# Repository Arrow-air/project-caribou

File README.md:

# Project Caribou 🦌

**An open-source heavy-lift hexacopter for cargo logistics and precision agriculture.**

Project Caribou is a ~200 kg MTOW hexacopter with ~100 kg payload capacity, 18–24S power architecture, and ArduPilot firmware. Designed for ruggedness, field repairability, and cost-effective manufacturing. Built on lessons from Project Feather and Project Quiver.

Developed by [Arrow Air](https://arrowair.com) and released under the CERN Open Hardware Licence.

## Key Features

- **Heavy lift** — ~100 kg payload for cargo delivery or 80L liquid spraying
- **Hybrid material airframe** — welded steel/aluminum core with detachable CF or aluminum motor arms
- **High-voltage architecture** — 18–24S (60–100V) with external HV kill switch and redundant power supply
- **Redundant avionics** — triple-redundant IMU, GPS, and compass
- **ArduPilot firmware** — standard QGroundControl/Mission Planner compatibility
- **Field serviceability** — modular arms for transport, replaceable components

## Repository Structure

```
project-caribou/
├── engineering/            # Active design work
│   ├── cad/                # build123d CAD, reference geometry, exports
│   └── electronics/        # Self-contained KiCad PCB projects
│       └── pcbs/
│           ├── CBC_PCB/    # Caribou battery connector PCB, issue #6
│           │   └── kicad/libs/
│           └── CMAIN_PCB/  # Caribou main PCB, issue #8
│               └── kicad/libs/
├── docs/
│   ├── ADRs/               # Architecture Decision Records
│   └── meetings/           # Meeting notes and summaries
├── src/                    # Legacy/general source area
└── CONTRIBUTING.md
```

## Community

- **Discord** — [discord.gg/arrow](https://discord.gg/arrow) — `#project-caribou-general`
- **DAO Forum** — [dao.arrowair.com](https://dao.arrowair.com)

## License

Everything in this repository is licensed under the **[CERN Open Hardware Licence Version 2 - Strongly Reciprocal (CERN-OHL-S v2)](LICENSE)**: the hardware design (CAD files, schematics, PCB layouts, manufacturing files and documentation) and the CBC firmware under `engineering/electronics/pcbs/CBC_PCB/firmware/`. The licence requires that derivative works remain open source under the same terms.

Source location: <https://github.com/Arrow-air/project-caribou>

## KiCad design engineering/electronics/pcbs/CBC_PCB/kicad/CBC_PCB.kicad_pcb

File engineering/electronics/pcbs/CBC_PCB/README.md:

# CBC_PCB — Caribou Battery Connector PCB

The Caribou Battery Connector PCB (CBC) interfaces 18S smart battery packs with the Caribou hexacopter electrical system. Each motor arm carries one CBC board connected to one battery, providing power switching, protection, voltage regulation, and dual CAN bus communication.

- **GitHub issue:** [#6 — Design BC-PCB for Caribou: 18S, 100A nominal, 200A spike](https://github.com/Arrow-air/project-caribou/issues/6)
- **Starting point:** Project Quiver BC-PCB KiCad design.
- **EDA Tool:** KiCad 10
- **Initial layout import:** KiCad source is in [`kicad/`](kicad/); import notes are in [`docs/import-2026-05-19-cbc-layout.md`](docs/import-2026-05-19-cbc-layout.md).

## Context within Project Caribou

Project Caribou is a ~200 kg MTOW heavy-lift hexacopter with ~100 kg payload capacity, 18–24S power architecture, and ArduPilot firmware. The aircraft uses 6× Hobbywing XRotor X15 propulsion units, each fed by a dedicated 18S Tattu 4.0 smart battery.

Each of the 6 motor arms has:
- 1× Tattu 4.0 18S battery pack
- **1× CBC_PCB** (this board) — battery interface, protection, regulation
- 1× Hobbywing XRotor X15 motor + ESC

The CBC board sits between the battery and the propulsion unit. It provides:
1. **Battery interface** — receives battery power and battery CAN via the [C90D adapter PCB](../C90D_PCB/), which mates the Tattu 4.0 battery connector
2. **Short-circuit protection** — 250A ceramic fuse
3. **Active power switching** — precharge, kill switch, power enable via MOSFETs
4. **Voltage regulation** — galvanically isolated 12V (GNDE) for the aircraft power distribution, plus non-isolated 5V/3.3V (GNDI) for onboard logic
5. **Dual CAN bus** — battery protocol (CAN 1) and DroneCAN (CAN 2) as bridge
6. **Wireless diagnostics** — WiFi/BLE via ESP32-S3 for configuration and monitoring

The regulated 12V output (GNDE) feeds into the Caribou Main PCB ([CMAIN_PCB](../CMAIN_PCB/)) via the JST JWPF signal connector (J501) harness.

## Concept Renderings

These early renderings show the intended CBC_PCB packaging concept and approximate component placement. They are illustrative only and may change during schematic/layout development.

## Board Overview

```
Battery (18S Tattu 4.0)
        |
        v
+---------------------+
|  C90D Adapter PCB    |  ← Separate board: mates the battery connector,
|  (../C90D_PCB/)      |     bridges present-detect pins
+---------------------+
        |
        v
+---------------------+
|  Power Entry Pads    |  ← Power (+ / −) via HC201/HC202 pads,
|  + Battery CAN       |     CAN L/H from battery via CN201
+---------------------+
|  AMXL-250 Fuse       |  ← 250A short-circuit protection
+---------------------+
|  MOSFETs             |  ← Precharge / Kill switch / Power enable
+---------------------+
|  Screw Terminals     |  ← Red (+) and Black (−) cables
|  (AMT0650009DB0000G) |     to Hobbywing X15 propulsion
+---------------------+
|                       |
|  HV Bus (54–75.6V)   |
|    |            |     |
|    v            v     |
|  [Buck]    [Push-Pull]|
|  5V/1A     12V/10A   |
|  (GNDI)    (isolated) |
|    |        (GNDE)    |
|    v            |     |
|  [LDO]         |     |
|  3.3V          |     |
|  (GNDI)        |     |
+---------------------+
|  JST JWPF Connector  |  ← 12V (GNDE), DroneCAN, signals
|  (J501, 8-pos)       |     to aircraft harness → CMAIN_PCB
+---------------------+
```

## Specifications

| Parameter | Value |
|---|---|
| Configuration | 18S (18 series cell groups) |
| Max Voltage | 75.6V (4.2V × 18) |
| Nominal Voltage | 64.8V (3.6V × 18) |
| Continuous Current | 150A (in line with the C90D power path) |
| Spike Current | 200A (short duration) |
| Board Shape | Rectangular |
| EDA Tool | KiCad 10 |
| Board Layers | TBD |

### Current Rating Justification

Based on the Hobbywing XRotor X15 motor data:

| Throttle | Thrust | Current per Motor |
|---|---|---|
| 51% | 27,257 g | 44.7 A |
| 72% | 47,933 g | 101.6 A |
| 100% | 72,647 g | 197.1 A |

Hover throttle is ~50%. The 150A continuous rating covers normal operations with margin; the 200A spike rating handles full-throttle bursts.

## Connectors and Fuse

### Battery Interface (via C90D Adapter)

The CBC does not mate the battery directly. The Tattu 4.0 pack connector mates with the [C90D adapter PCB](../C90D_PCB/), which carries the battery connector (ACES 59626), bridges the battery-present detection pins, and adapts the connector orientation into the CBC assembly.

From the C90D, the battery reaches the CBC through:

| Interface | Reference | Function |
|---|---|---|
| Power entry pads | HC201 (`H_PWR-IN`), HC202 (`H_PWR-IN--PREFUSE`) | High-current + / − power path from the C90D |
| Battery CAN connector | CN201 (A1257WV-S-2P, 2-pin GH-compatible) | `CANH_BAT` / `CANL_BAT` to the isolated battery CAN interface |

> **Note:** the battery-present detection bridge (required for the Tattu pack to power on) lives on the C90D side — see the C90D documentation for connector and mating details.

### Propulsion Screw Terminals

**Selected: Amphenol Anytek AMT0650009DB0000G**

These are the high-current screw terminals where cables to the Hobbywing X15 propulsion system are connected (+ and −).

| Parameter | Value |
|---|---|
| Type | Screw Terminal, Power Tap |
| Screw Size | M5 |
| Pins | 6 |
| Current Rating | 180A |
| Mounting | Through-Hole DIP |
| Contact Material | Brass + Steel Nut (matte tin plated) |
| Torque | 18 lbf·in |

Two sets of AMT0650009DB0000G screw terminals are used on the board: one pair for the propulsion output (+ / −), and another pair for mounting the main fuse.

### Signal Connector (Drone Interface)

**Selected: JST B08B-JWPF-SK-R (J501)**

This connector interfaces the CBC with the rest of the Caribou electrical system via a wiring harness to the [CMAIN_PCB](../CMAIN_PCB/). The JWPF series is a waterproof wire-to-board connector family; an earlier Amphenol AT13 concept was dropped in favor of JST.

| Pin | Signal | Function |
|---|---|---|
| 1 | GNDE | Isolated ground |
| 2 | GNDE | Isolated ground |
| 3 | 12V_ISOLATED | Isolated 12V output to aircraft LV system |
| 4 | 12V_ISOLATED | Isolated 12V output to aircraft LV system |
| 5 | CANL_DRONE | DroneCAN low |
| 6 | CANH_DRONE | DroneCAN high |
| 7 | 12V_TRIGGER_SIG | Kill switch trigger signal |
| 8 | 12V_SUPPLY | 12V supply input |

The 8 positions carry the isolated 12V output (GNDE), the DroneCAN bus pair, and the kill/control signals to/from the Caribou avionics.

### Main Fuse (Short-Circuit Protection)

**Selected: Eaton AMXL-250**

The main fuse sits between the battery connector and the power output stage, protecting against short circuits. It is mounted on two AMT0650009DB0000G screw terminals (bolt-in design).

| Parameter | Value |
|---|---|
| Type | Automotive bolt-in fuse |
| Current Rating | 250A |
| Voltage Rating | 125 Vdc |
| Body | Ceramic |
| Mounting | Bolt-in (M5 terminals) on 2× AMT0650009DB0000G |

The 250A fuse rating provides short-circuit protection while allowing the full 200A spike current without nuisance blowing. The ceramic body handles the thermal demands of high-current interruption.

## MCU and Communication

### MCU: ESP32-S3-WROOM-1 (U301)

The ESP32-S3-WROOM-1 module (N16R8 variant) is a dual-core microcontroller with integrated wireless connectivity. It includes a PCB antenna — no external antenna components are required. A keepout zone must be maintained around the antenna area on the PCB layout (no copper / ground plane underneath).

| Parameter | Value |
|---|---|
| Core | 2× 32-bit Xtensa LX7, up to 240 MHz |
| Flash | 16 MB (N16R8) |
| PSRAM | 8 MB (N16R8) |
| WiFi | 802.11 b/g/n (2.4 GHz) |
| Bluetooth | BLE 5.0 |
| Operating Voltage | 3.0–3.6V |
| Antenna | Integrated PCB antenna |

### Dual CAN Bus (2× MCP2515 + Transceiver)

Two independent CAN networks using external MCP2515 controllers on a shared SPI bus. This provides identical timing behavior on both buses and clean separation of the battery-side and drone-side CAN domains.

| CAN Bus | Purpose | Controller | Transceiver |
|---|---|---|---|
| CAN 1 — Battery | Battery protocol (smart battery communication) | MCP2515 (U402, SPI, CS1) | ADM3053BRWZ (U404, galvanically isolated) |
| CAN 2 — Drone | DroneCAN (UAVCAN v0) interface to Caribou avionics | MCP2515 (U401, SPI, CS2) | TJA1049T/3J (U403) |

The battery CAN transceiver (ADM3053) has an integrated isolated DC-DC converter, so the battery-side CAN domain is galvanically isolated from the board logic. Each MCP2515 is clocked by a 16 MHz crystal (X401/X402). 120 Ω termination resistors are jumper-selectable and open by default.

The board converts between the battery protocol (CAN 1) and DroneCAN (CAN 2). The DroneCAN bus connects via the J501 signal connector through the wiring harness to the [CMAIN_PCB](../CMAIN_PCB/), which serves as the central avionics hub for all 6 motor arms.

### Schematic Sheet Interfaces

| Signal / rail | Source sheet | Destination sheet(s) | Direction / notes |
|---|---|---|---|
| `H_PWR-IN`, `H_PWR-IN-`, `H_PWR-IN--PREFUSE` | POWER SECTION | POWER SECTION / board power path | 18S battery high-current domain; main fuse is mounted on two of the AMT screw terminals (J201–J204). |
| `+5V` | POWER REGULATOR | ESP32 SECTION, CAN SECTION, PERIPHERALS | Internal non-isolated logic rail. |
| `+3V3` | POWER REGULATOR | ESP32 SECTION, CAN SECTION, PERIPHERALS | ESP32, MCP2515, CAN transceivers, sensors. |
| `12V_ISOLATED` | POWER REGULATOR | PERIPHERALS / J501 connector | Isolated output to aircraft harness; add an output fuse before harness output. |
| `ESP_ENABLE_SIGNAL` | ESP32 SECTION | POWER SECTION | ESP-controlled main MOSFET latch enable (latch: `U201` 74LVC2G02); latch output default-low via `R207` pulldown. |
| `PRECHARGE_ESP_SIGNAL` | ESP32 SECTION | POWER SECTION | ESP-controlled precharge command. |
| `SCHMITT_OUT` | POWER SECTION | ESP32 SECTION | Hardware kill/trigger state feedback to ESP32. |
| `SCK`, `MOSI`, `MISO` | ESP32 SECTION / CAN SECTION | ESP32 ↔ dual MCP2515 | Shared SPI bus; `SCK`/`MOSI` from ESP32, `MISO` from MCP2515s. |
| `CS#1`, `CS#2` | ESP32 SECTION | CAN SECTION | MCP2515 chip-selects; add pull-ups so controllers remain deselected during ESP32 reset/boot. |
| `INT#1`, `INT#2` | CAN SECTION | ESP32 SECTION | MCP2515 interrupt outputs; ESP32 pull-up usage is documented in firmware/hardware notes. |
| `RESET1`, `RESET2` | ESP32 SECTION | CAN SECTION | MCP2515 resets from ESP32. |
| `TEMP1_DQ`, `TEMP2_DQ` | ESP32 SECTION / PERIPHERALS | ESP32 ↔ temperature sensors | 1-Wire data nets; formerly `DATA1` / `DATA2`. |
| `CANH_BAT`, `CANL_BAT` | CAN SECTION / POWER SECTION | Battery connector ↔ CAN 1 | Battery CAN pair only; no battery CAN ground is normally carried. |
| `CANH_DRONE`, `CANL_DRONE` | CAN SECTION / PERIPHERALS | CAN 2 ↔ J501 harness | DroneCAN pair to CMAIN_PCB; termination is jumper-selectable and normally open. |
| `GND_CA`, `GND_CB`, `GNDI`, `GNDE` | Multiple | Domain-specific returns | `GND_CA` is effectively unused unless battery CAN reference is later required. `GND_CB` may be tied with other CBC `GND_CB` references on CMAIN_PCB. |

### GPIO Allocation

As routed on the ordered board (from the production netlist):

| Function | Signal | ESP32-S3 GPIO |
|---|---|---|
| Precharge command | `PRECHARGE_ESP_SIGNAL` | IO4 |
| Kill/trigger state feedback | `SCHMITT_OUT` | IO5 |
| Main MOSFET latch enable | `ESP_ENABLE_SIGNAL` | IO6 |
| Temperature sensors (1-Wire, DS18B20) | `TEMP2_DQ` / `TEMP1_DQ` | IO7 / IO15 |
| Shared SPI — MOSI, SCK, MISO | `MOSI` / `SCK` / `MISO` | IO11 / IO12 / IO13 |
| MCP2515 #1 (Battery CAN) — CS, INT, RESET | `CS#1` / `INT#1` / `RESET1` | IO10 / IO21 / IO48 |
| MCP2515 #2 (Drone CAN) — CS, INT, RESET | `CS#2` / `INT#2` / `RESET2` | IO14 / IO47 / IO9 |

## Functional Requirements

### Power Path

- **High-side MOSFET switching** — N-channel MOSFETs with charge pump gate drive
- **Precharge circuit** — soft-start via resistor + relay/MOSFET to limit inrush current
- **Emergency kill switch** — hardware-level kill input, independent of MCU. Connects to the Caribou external HV kill switch via the AT signal connector.
- **Main fuse** — Eaton AMXL-250 (250A) bolt-in fuse for short-circuit protection

### Voltage Regulation

The power supply architecture uses two independent stages with full galvanic isolation between internal onboard logic (GNDI) and external drone systems (GNDE).

#### Internal Supply (GNDI — non-isolated)

Provides power for onboard logic (ESP32, MCP2515, CAN transceivers, gate drivers, sensors).

| Stage | Topology | IC | Input | Output | Notes |
|---|---|---|---|---|---|
| 5V Rail | Sync Buck | e.g. MP9487 or similar (100V+, integrated FETs, ≥1A) | 54–75.6V (HV Bus) | 5V / 1A | Main internal rail |
| 3.3V Rail | LDO | e.g. AMS1117-3.3 or similar | 5V | 3.3V | ESP32, MCP2515, CAN transceivers |

#### External Supply (GNDE — galvanically isolated)

Provides isolated 12V output for the Caribou aircraft power distribution via the [CMAIN_PCB](../CMAIN_PCB/).

| Stage | Topology | IC | Input | Output | Notes |
|---|---|---|---|---|---|
| 12V Rail | Isolated Push-Pull | TBD | 54–75.6V (HV Bus) | 12V / 10A (isolated, GNDE) | Powers aircraft avionics, sensors, servos via CMAIN_PCB |

The isolation barrier between GNDI and GNDE ensures that a fault on the aircraft power bus does not back-feed into the battery management logic.

## Folder Layout

```
CBC_PCB/
├── README.md               ← this file
├── docs/                   ← board-specific notes, requirements, design docs
│   ├── connector-pinout.md ← connector/harness pinout and wiring notes
│   ├── power-architecture.md ← power tree and protection notes
│   ├── pt1.5-changes.md    ← PT1.5 changes: precharge ground fix, sensing, buzzer, aux inrush
│   └── schematic-review-followup.md ← schematic review action register
├── firmware/               ← board-specific firmware (ESP32-S3)
├── images/                 ← board renders, screenshots, diagrams, photos
├── kicad/                  ← KiCad 10 project files
│   ├── libs/               ← project-local KiCad libraries
│   │   ├── 3dmodels/       ← project-local 3D models
│   │   ├── CBC_PCB.pretty/ ← project-local footprint library
│   │   └── CBC_PCB.kicad_sym ← project-local symbol library
│   └── production/         ← JLC fab outputs: Gerber zip, BOM, positions, netlist
└── manufacturing/          ← board STEP (zipped, CBC_PCB.step.zip) and fab toolkit options
```

## Related

- [CMAIN_PCB](../CMAIN_PCB/) — Caribou Main PCB (central avionics hub)
- [Project Caribou](https://github.com/Arrow-air/project-caribou) — parent project
- [Issue #6](https://github.com/Arrow-air/project-caribou/issues/6) — tracking issue for this board
- [Issue #8](https://github.com/Arrow-air/project-caribou/issues/8) — CMAIN_PCB tracking issue

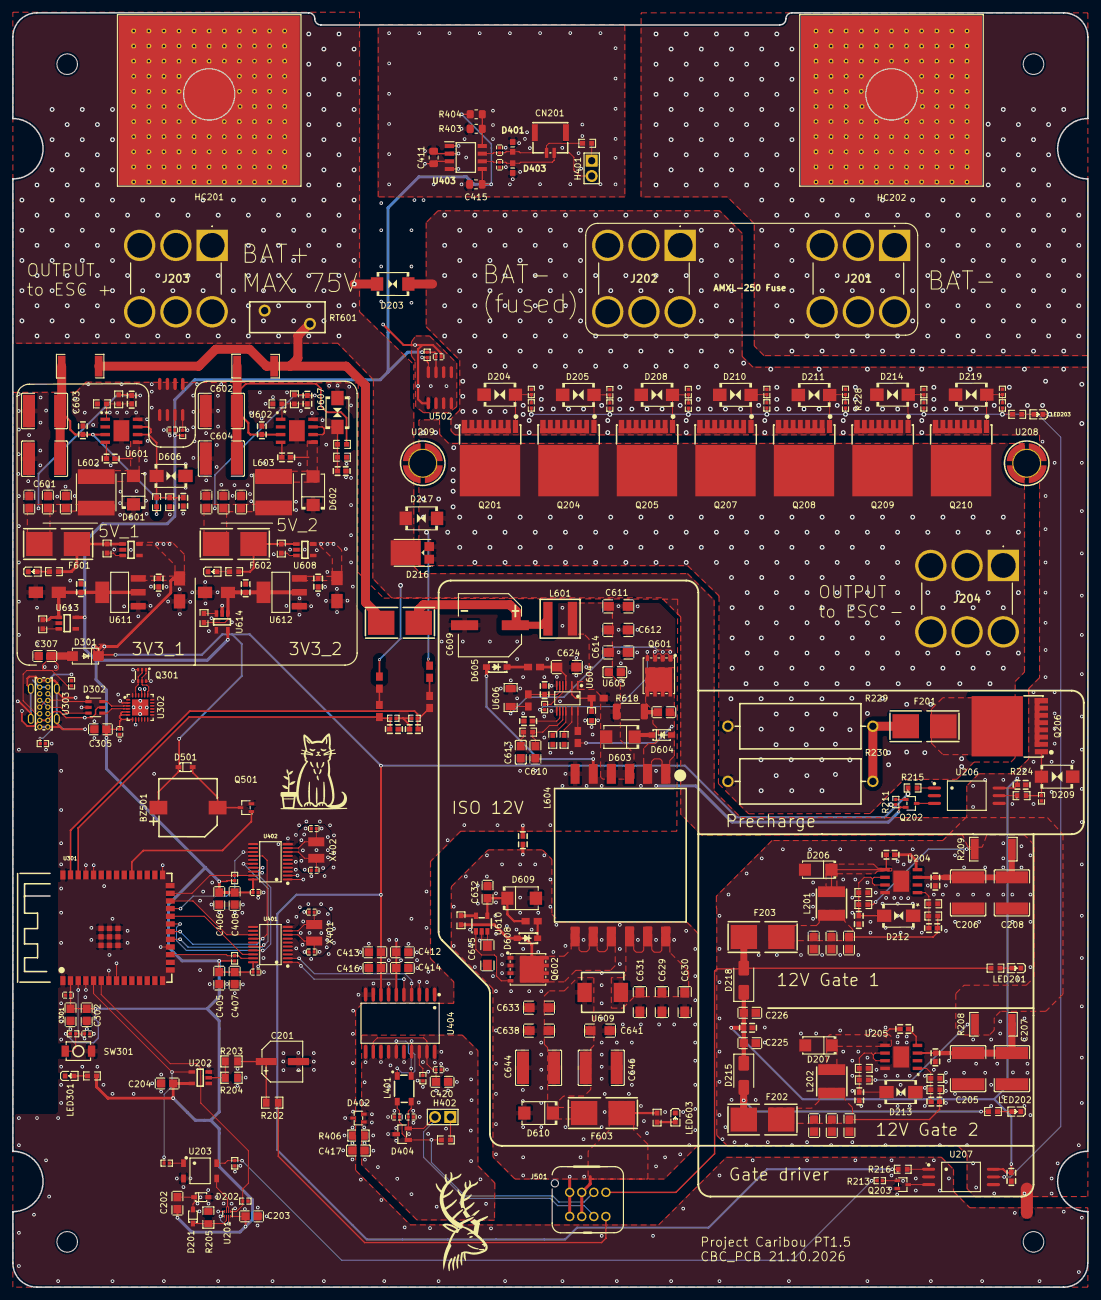
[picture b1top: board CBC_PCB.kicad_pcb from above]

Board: 6 copper layers, 178.0 x 211.0 mm, 317 parts (0 on the bottom side), 159 nets.

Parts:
BZ501: GSD9605YB-5V2800; BUZ-SMD_GSD9605YB-5V2800
C201: 100uF; CAP-SMD_BD6.3-L6.6-W6.6-LS7.4-FD
C202, C632: 1uF; C0805
C203, C204, C302, C305, C307, C407, C408, C414, C416, C420: 10uF; C0805
C205, C206, C207, C208, C601, C602, C603, C604, C644, C646: 2.2uF; C2220
C209, C210, C211, C212, C213, C214, C215, C216, C223, C224, C227, C228, C229, C605, C606, C607, C608, C616, C617, C626, C627, C634, C635, C639, C640: 100nF; C0603
C217, C218, C219, C220, C221, C222, C225, C226, C301, C405, C406, C412, C413, C618, C619, C620, C621, C622, C623: 4.7uF; C0805
C303: 1uF; C0402
C304, C306, C409, C410, C421, C501, C502: 100nF; C0402
C401, C402, C403, C404: 22pF; C0402
C411, C415: 100nF; C_0805_2012Metric_Pad1.18x1.45mm_HandSolder
C417: 100pF; C0805
C418, C419, C422, C423: 220pF; C0402
C609: 47uF; CAP-SMD_BD10.0-L10.3-W10.3-FD-LS11.0
C610: 470pF; C0805
C611, C612, C614, C624, C645: 4.7uF; C1206
C613: 33nF; C0805
C615: 220nF; C0603
C625: 47pF; C0603
C628: 4.7nF; C0603
C629, C630, C631, C633, C638, C641: 47uF; C1206
C636, C637, C642, C643: 10uF; CAP-SMD_L3.5-W2.8-R-RD
CN201: CONN-SMD_A1257WV-S-2P
D201, D202: SOD-323_L1.8-W1.3-LS2.5-RD
D203, D217: SMBJ78CA; SMB_L4.3-W3.6-LS5.4-BI
D204, D205, D208, D209, D210, D211, D214, D219: SMB_L4.6-W3.6-LS5.4-BI
D206, D207: SMA_L4.3-W2.6-LS5.2-RD
D212, D213, D606, D607: SMB_L4.6-W3.6-LS5.3-BI
D215, D218: SS34; D_SMA
D216: FSV10150V; C719814_TO-277A_L5_9-W4_4-LS6_5-TR
D301: SMA_L4.3-W2.6-LS5.0-FD
D302: SOT-23-6_L2.9-W1.6-P0.95-LS2.8-BL
D401, D403: PESD0603-240; DIONC1608X55N
D402: SOT-323-3_L2.0-W1.3-P1.30-LS2.1-BR
D404: SOT-23-3_L2.9-W1.3-P1.90-LS2.4-BL-2
D501: 1N4148WS; SOD-323_L1.8-W1.3-LS2.5-RD
D601, D602, D609, D610: SMB_L4.6-W3.6-LS5.3-RD
D603: SMBJ58A; SMB_L4.6-W3.6-LS5.3-RD
D604: SOD-123FL_L2.8-W1.8-LS3.8-RD
D605, D608: SOD-123_L2.7-W1.6-LS3.7-RD-1
F201, F603: 0154005.DR; FUSE-SMD_L9.8-W5.1
F202, F203, F601, F602: FUSE-SMD_L9.8-W5.1
F604: 0154003.DRT; FUSE-SMD_L9.8-W5.1
H401, H402: HDR-TH_2P-P2.54-V-M
HC201, HC202: C90D_PAD
J201, J202, J203, J204: AMT0650009DB0000G
J501: B08B-JWPF-SK-R
L201, L202: 33uH; IND-SMD_L5.0-W5.0-P3.60_SMNR5040
L401: FILTER-SMD_4P-L4.5-W3.2_ACT45B-510-2P
L601: 22uH; IND-SMD_L6.6-W6.4
L602, L603: 33uH; IND-SMD_L6.0-W6.0_SMNR6045
L604: 20.5uH; XFMR-SMD_12P-L22.1-W21.8-P3.00-LS29.2-BL
LED201, LED202, LED203, LED301, LED601, LED602, LED603: LED0603-RD
NT201: NetTie_2; NetTie-2_SMD_Pad2.0mm
Q201, Q205, Q206, Q207, Q208, Q209, Q210: TOLL-8_L10.4-W9.9-P1.20-LS11.7-BL
Q202, Q203, Q501: LMUN5235T1G; C2846922_SOT-323-3_L2_0-W1_3-P1_30-LS2_1-BR
Q204: SP015N03BGHTO; TOLL-8_L10.4-W9.9-P1.20-LS11.7-BL
Q301: SC-70-6_L2.2-W1.3-P0.65-LS2.1-BR
Q601, Q602: DFN-8_L5.9-W5.2-P1.27-LS6.2-BL
R201, R207, R212, R217, R223, R226, R227, R235, R237, R242, R245, R248, R301, R401, R402: 10kΩ; R0402
R202: 15kΩ; R0805
R203: 120kΩ; R0805
R204: 36kΩ; R0805
R205: 10kΩ; R0805
R206: 330Ω; R0402
R208, R209, R628, R629: 10Ω; R2512
R210, R214, R218, R225, R228, R236, R240: 100Ω; C25076_R0402
R211, R213: 0; C106231_R0402
R215, R216: 300; C114617_R0603
R219, R221: 590K, 0603; R0603
R220, R222, R232, R234, R605, R607, R614, R616: 10kΩ; R0603
R224: 20; C125758_R0603
R229, R230: 33Ω; RES-TH_BD7.5-L20.0-P24.00-D1.0
R231, R233, R613, R615: 140kΩ; R0603
R238, R239, R241, R625: 1.8kΩ; R0603
R243, R244, R246, R247, R610: 160kΩ; R0805
R302: 39Ω; R0603
R303, R304: 5.1kΩ; R0402
R403: 0R; R_0805_2012Metric_Pad1.20x1.40mm_HandSolder
R404: 10K; R_0805_2012Metric_Pad1.20x1.40mm_HandSolder
R405, R408: 120Ω; R0603
R406: 1MΩ; R0805
R407, R611: 0Ω; R0402
R501, R502: 4.7kΩ; R0402
R601: 6.04kΩ; R0603
R602: 60.4kΩ; R0603
R603: 7.5kΩ; R0603
R604, R606: 240kΩ; R0603
R608: 1.2MΩ; R0805
R609: 51kΩ; R0603
R612: 68Ω; R0805
R617, R623: 3Ω; R0805
R618: 100Ω; R_2010_5025Metric
R619, R621, R626, R627: 100Ω; R0603
R620, R622: 390Ω; R0603
R624: 2.37kΩ; R0603
RT601: NTC 10D-15; RES-TH_L12.5-W5.1-P7.50-D1.2-S2.20
SW301: SW-SMD_L3.9-W3.0-P4.45
U201: 74LVC2G02HK3-7; UDFN-8_L1.5-W1.0-P0.35-BL
U202: 74LVC1G17W5-7; SOT-25-5_L3.0-W1.8-P0.95-LS3.0-BL
U203: CPC1106NTR; SOP-4_L4.1-W3.8-P2.54-LS6.1-BL
U204, U205, U601, U602: MP9486GN-Z; SOIC-8EP_MP9486_MNP
U206, U207: ICPL-314P-500EAXW; C42432174_SOP-6_L6_8-W4_6-P1_27-LS11_7-BL
U208, U209: BSMTSOM330BTR; SMD_BD6.0-D4.2
U301: 2.4GHz; WIRELM-SMD_ESP32-S3-WROOM-1
U302: QFN-24_L4.0-W4.0-P0.50-BL-EP2.7
U303: USB-C-TH_HANBO_MC-118LD-H65
U401, U402: TSSOP-20_L6.5-W4.4-P0.65-LS6.4-BL
U403: TJA1049T/3J; SOIC127P600X175-8N
U404: ADM3053BRWZ-REEL7; SOIC-20_L13.0-W7.6-P1.27-LS10.3-BL
U501, U502: SOIC-8_L4.9-W3.9-P1.27-LS6.0-BL
U603: 1uF; C0805
U604: MSOP-16_12P-L4.0-W3.0-P0.50-LS4.9-BL
U605: 120pF; C0805
U606: 10mΩ; R1206
U607, U608, U613, U614: MAX40203AUK+T; MAX40203AUK_T_SOT-23-5
U609: IND-SMD_L7.0-W6.6
U610: TSOT-23-5_L2.9-W1.6-P0.95-LS2.8-BR
U611, U612: SOT-223-3_L6.5-W3.4-P2.30-LS7.0-BR
X401, X402: 16MHz; CRYSTAL-SMD_L3.2-W2.5_3225-8MHZ

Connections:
12V_GATE_P1: C215.2, C217.2, C219.2, C221.2, F203.1, L201.2, R219.2
12V_GATE_P2: C216.2, C218.2, C220.2, C222.2, F202.1, L202.2, R221.2
12V_GATE_V: C213.2, C214.2, C225.2, C226.2, C227.2, D215.1 (K), D218.1 (K), U206.6 (VCC), U207.6 (VCC)
12V_ISOLATED: F603.2, J501.3, J501.4, R625.2
12V_Supply: D218.2 (A), F203.2, J501.8, R238.1
12V_TRIGGER_SIG: J501.7, R202.1
+3V3: C202.2, C203.2, C204.2, C301.2, C302.2, C304.2, C305.2, C306.2, C405.2, C406.2, C407.2, C408.2, C409.2, C410.2, C412.2, C414.2, C415.1, C501.2, C502.2, R301.2, R302.2, R401.2, R402.2, R404.1, R501.2, R502.2, U201.8 (VCC), U202.5 (VCC), U301.2 (3V3), U302.5 (VIO), U302.6 (VDD), U302.7 (REGIN), U401.20 (VDD), U402.20 (VDD), U403.5 (VIO), U404.6 (VIO), U501.3 (VDD), U502.3 (VDD), U613.5 (OUT), U614.5 (OUT)
+3V3_P1: C634.1, C636.1, R626.1, U611.2 (VOUT), U611.4 (VOUT), U613.1 (VDD)
+3V3_P2: C635.1, C637.1, R627.1, U612.2 (VOUT), U612.4 (VOUT), U614.1 (VDD)
+5V: BZ501.1 (+), C411.2, C413.2, C416.2, C639.1, C640.1, C642.1, C643.1, D301.2 (K), D501.1 (K), R215.1, R216.1, U403.3 (VDD), U404.8 (VCC), U607.5 (OUT), U608.5 (OUT), U611.3 (VIN), U612.3 (VIN)
+5V_P1: C616.2, C618.2, C620.2, C622.2, F601.1, L602.2, R604.2
+5V_P2: C617.2, C619.2, C621.2, C623.2, F602.1, L603.2, R606.2
/CAN SECTION/RXD: U402.2 (RXCAN), U403.4 (RX)
/CAN SECTION/RXD2: U401.2 (RXCAN), U404.4 (RXD)
/CAN SECTION/TXD: U402.1 (TXCAN), U403.1 (TX)
/CAN SECTION/TXD2: U401.1 (TXCAN), U404.5 (TXD)
/ESP32 SECTION/D+: D302.6, U302.3 (D+)
/ESP32 SECTION/D-: D302.4, U302.4 (D-)
/ESP32 SECTION/DP_N: D302.3, U303.A7 (D-), U303.B7 (D-)
/ESP32 SECTION/DP_P: D302.1, U303.A6 (D+), U303.B6 (D+)
/ESP32 SECTION/DTR: Q301.2 (B), Q301.4 (E), U302.23 (DTR)
/ESP32 SECTION/GPIO0: Q301.3 (C), U301.27 (IO0)
/ESP32 SECTION/RESET: C303.2, Q301.6 (C), R301.1, SW301.1, U301.3 (EN)
/ESP32 SECTION/RTS: Q301.1 (E), Q301.5 (B), U302.19 (RTS)
/ESP32 SECTION/RXD0: U301.36 (RXD0), U302.21 (TXD)
/ESP32 SECTION/TXD0: U301.37 (TXD0), U302.20 (RXD)
/POWER SECTION/MOSFET_CONTROL_SIGNAL: R207.2, R213.1, U203.4 (Load)
/POWER SECTION/SWITCHED_GATE_V: R210.1, R214.1, R218.1, R225.1, R228.1, R236.1, R240.1, R241.1, U207.5 (VO)
BUZZER: Q501.1 (B), U301.31 (IO38)
CANH_BAT: C418.2, CN201.1, D401.1 (K), R405.2, U403.7 (CANH)
CANH_DRONE: C422.2, D404.1, J501.6, L401.2, R408.2
CANL_BAT: C419.1, CN201.2, D403.1 (K), H401.2, U403.6 (CANL)
CANL_DRONE: C423.1, D404.2, H402.2, J501.5, L401.3
CS#1: U301.18 (IO10), U402.18 (CS#)
CS#2: U301.22 (IO14), U401.18 (CS#)
ESP_ENABLE_SIGNAL: R201.2, U201.1 (1A), U301.6 (IO6)
GND: C201.2, C203.1, C204.1, C228.1, C229.1, C301.1, C302.1, C303.1, C304.1, C305.1, C306.1, C307.1, C401.1, C402.1, C403.1, C404.1, C405.1, C406.1, C407.1, C408.1, C409.1, C410.1, C411.1, C412.1, C413.1, C414.1, C415.2, C416.1, C417.1, C418.1, C419.2, C501.1, C502.1, C601.1, C602.1, C603.1, C604.1, C605.2, C606.2, C609.2, C610.1, C611.1, C612.1, C613.2, C614.1, C615.1, C618.1, C619.1, C620.1, C621.1, C622.1, C623.1, C624.1, C625.1, C626.1, C627.1, C628.1, C634.2, C635.2, C636.2, C637.2, C639.2, C640.2, C642.2, C643.2, D202.2 (A), D302.2, D401.2 (A), D402.3, D403.2 (A), D601.1 (A), D602.1 (A), D606.1 (K), D607.1 (K), L604.6, LED301.1 (K), LED601.1 (K), LED602.1 (K), NT201.1, Q202.2 (E), Q203.2 (E), Q501.2 (E), R201.1, R204.1, R205.1, R207.1, R245.1, R248.1, R303.1, R304.1, R403.1, R406.1, R601.1, R602.1, R605.1, R607.1, R609.1, R614.1, R616.1, SW301.2, U201.4 (GND), U202.3 (GND), U203.2 (-Control), U301.1 (GND), U301.40 (GND), U301.41 (GND), U302.2 (GND), U302.25 (EPAD), U303.13 (EH), U303.A1 (GND), U303.A12 (GND), U303.B1 (GND), U303.B12 (GND), U401.10 (VSS), U402.10 (VSS), U403.2 (GND), U404.1 (GND1), U404.3 (GND1), U404.7 (GND1), U404.9 (GND1), U404.10 (GND1), U501.5 (GND), U502.5 (GND), U601.8 (GND), U602.8 (GND), U603.2, U604.8 (GND), U604.9 (GND), U606.1, U607.2 (GND), U608.2 (GND), U611.1 (GND), U612.1 (GND), U613.2 (GND), U614.2 (GND)
GNDE: C628.2, C629.1, C630.1, C631.1, C632.1, C633.1, C638.1, C641.1, C644.1, C645.1, C646.1, D609.2 (A), D610.2, J501.1, J501.2, LED603.1 (K), Q602.1 (S), U610.2 (GND)
GND_CD: C417.2, C420.1, C421.1, C422.1, C423.2, D402.1, D402.2, D404.3, R406.2, R407.2, U404.11 (GND2), U404.13 (GND2), U404.16 (GND2), U404.20 (GND2)
HV_BUS_SENSE: C229.2, R247.2, R248.2, U301.38 (IO2)
H_PWR-IN: D203.1, D216.3 (K), D217.1, HC201.1 (1_1), J203.1, J203.2, J203.3, J203.4, J203.5, J203.6, R208.2, R209.2, R231.2, R233.2, R246.1, RT601.1
H_PWR-IN-: C205.1, C206.1, C207.1, C208.1, C209.2, C210.2, C213.1, C214.1, C217.1, C218.1, C219.1, C220.1, C221.1, C222.1, C223.1, C224.1, C225.1, C226.1, C227.1, D203.2, D204.1, D205.1, D206.2 (A), D207.2 (A), D208.1, D209.1, D210.1, D211.1, D212.1 (K), D213.1 (K), D214.1, D219.1, J202.1, J202.2, J202.3, J202.4, J202.5, J202.6, LED201.1 (K), LED202.1 (K), LED203.1 (K), NT201.2, Q201.2 (S), Q201.3 (S), Q201.4 (S), Q201.5 (S), Q201.6 (S), Q201.7 (S), Q201.8 (S), Q204.2 (S), Q204.3 (S), Q204.4 (S), Q204.5 (S), Q204.6 (S), Q204.7 (S), Q204.8 (S), Q205.2 (S), Q205.3 (S), Q205.4 (S), Q205.5 (S), Q205.6 (S), Q205.7 (S), Q205.8 (S), Q206.2 (S), Q206.3 (S), Q206.4 (S), Q206.5 (S), Q206.6 (S), Q206.7 (S), Q206.8 (S), Q207.2 (S), Q207.3 (S), Q207.4 (S), Q207.5 (S), Q207.6 (S), Q207.7 (S), Q207.8 (S), Q208.2 (S), Q208.3 (S), Q208.4 (S), Q208.5 (S), Q208.6 (S), Q208.7 (S), Q208.8 (S), Q209.2 (S), Q209.3 (S), Q209.4 (S), Q209.5 (S), Q209.6 (S), Q209.7 (S), Q209.8 (S), Q210.2 (S), Q210.3 (S), Q210.4 (S), Q210.5 (S), Q210.6 (S), Q210.7 (S), Q210.8 (S), R212.1, R217.1, R220.1, R222.1, R223.1, R226.1, R227.1, R232.1, R234.1, R235.1, R237.1, R242.1, U204.8 (GND), U205.8 (GND), U206.4 (VSS), U207.4 (VSS)
H_PWR-IN--PREFUSE: HC202.1 (1_1), J201.1, J201.2, J201.3, J201.4, J201.5, J201.6
H_PWR-IN_5V_P1: C601.2, C603.2, C605.1, R613.2, R628.2, U601.3 (VIN)
H_PWR-IN_5V_P2: C602.2, C604.2, C606.1, R615.2, R629.2, U602.3 (VIN)
H_PWR-IN_AUX: F604.1, R628.1, R629.1, RT601.2
H_PWR-IN_ISO: C609.1, F604.2, L601.1
H_PWR-OUT-: D216.1 (A), D216.2 (A), D217.2, J204.1, J204.2, J204.3, J204.4, J204.5, J204.6, Q201.9 (D), Q204.9 (D), Q205.9 (D), Q207.9 (D), Q208.9 (D), Q209.9 (D), Q210.9 (D), R229.2, R230.2, R243.1
INT#1: U301.23 (IO21), U402.13 (INT#)
INT#2: U301.24 (IO47), U401.13 (INT#)
INTVCC: C624.2, R612.1, U604.5 (INTVCC)
MISO: U301.21 (IO13), U401.17 (SO), U402.17 (SO)
MOSI: U301.19 (IO11), U401.16 (SI), U402.16 (SI)
unnamed: BZ501.2 (-), D501.2 (A), Q501.3 (C)
unnamed: C613.1, R603.1
unnamed: C629.2, C630.2, C631.2, L604.10, L604.11, L604.12, U609.1
unnamed: C633.2, C638.2, C641.2, C644.2, C646.2, D610.1, F603.1, U609.2
unnamed: C202.1, D201.2 (A), D202.1 (K)
unnamed: D201.1 (K), R205.2, U201.6 (2B)
unnamed: C211.1, D206.1 (K), L201.1, U204.5 (SW)
unnamed: C212.1, D207.1 (K), L202.1, U205.5 (SW)
unnamed: C223.2, D212.2 (A), R231.1, R232.2, U204.6 (DIM), U204.7 (EN)
unnamed: C224.2, D213.2 (A), R233.1, R234.2, U205.6 (DIM), U205.7 (EN)
unnamed: D215.2 (A), F202.2, R239.1
unnamed: C607.1, D601.2 (K), L602.1, U601.5 (SW)
unnamed: C608.1, D602.2 (K), L603.1, U602.5 (SW)
unnamed: C611.2, C612.2, C614.2, D603.2 (A), L601.2, L604.3, L604.4, R608.2, R618.2, U603.1, U604.1 (VIN)
unnamed: D603.1 (K), D604.1 (K)
unnamed: D604.2 (A), L604.1, L604.2, Q601.3 (D), R610.2, U605.1
unnamed: D605.2 (A), L604.5
unnamed: D605.1 (C), R612.2
unnamed: C626.2, D606.2 (A), R613.1, R614.2, U601.6 (DIM), U601.7 (EN)
unnamed: C627.2, D607.2 (A), R615.1, R616.2, U602.6 (DIM), U602.7 (EN)
unnamed: D608.2 (A), L604.7, L604.8, L604.9, Q602.3 (D), R624.1
unnamed: D608.1 (C), R623.1
unnamed: C632.2, D609.1 (K), R623.2, U610.4 (VCC)
unnamed: F201.2, R229.1, R230.1
unnamed: H401.1, R405.1
unnamed: H402.1, R408.1
unnamed: LED201.2 (A), R238.2
unnamed: LED202.2 (A), R239.2
unnamed: LED203.2 (A), R241.2
unnamed: LED301.2 (A), R302.1
unnamed: LED601.2 (A), R620.2
unnamed: LED602.2 (A), R622.2
unnamed: LED603.2 (A), R625.1
unnamed: D204.2, Q201.1 (G), R210.2, R212.2
unnamed: Q202.1 (B), R211.2
unnamed: Q202.3 (C), U206.3 (C)
unnamed: Q203.1 (B), R213.2
unnamed: Q203.3 (C), U207.3 (C)
unnamed: D205.2, Q204.1 (G), R214.2, R217.2
unnamed: D208.2, Q205.1 (G), R218.2, R223.2
unnamed: F201.1, Q206.9 (D)
unnamed: D209.2, Q206.1 (G), R224.2, R226.2
unnamed: D210.2, Q207.1 (G), R225.2, R227.2
unnamed: D211.2, Q208.1 (G), R228.2, R235.2
unnamed: D214.2, Q209.1 (G), R236.2, R237.2
unnamed: D219.2, Q210.1 (G), R240.2, R242.2
unnamed: Q601.2 (G), R611.2
unnamed: Q601.1 (S), R617.2, U606.2
unnamed: Q602.2 (G), U610.1 (GATE)
unnamed: R243.2, R244.1
unnamed: R246.2, R247.1
unnamed: R618.1, U605.2
unnamed: U201.2 (1B), U201.3 (2Y), U203.3 (Load)
unnamed: U201.5 (2A), U201.7 (1Y)
unnamed: R203.1, R204.2, U202.2 (A)
unnamed: R206.1, U203.1 (+Control)
unnamed: C211.2, U204.4 (BST)
unnamed: C215.1, R219.1, R220.2, U204.1 (FB)
unnamed: C206.2, C208.2, C209.1, R209.1, U204.3 (VIN)
unnamed: C212.2, U205.4 (BST)
unnamed: C216.1, R221.1, R222.2, U205.1 (FB)
unnamed: C205.2, C207.2, C210.1, R208.1, U205.3 (VIN)
unnamed: R215.2, U206.1 (A)
unnamed: R224.1, U206.5 (VO)
unnamed: R216.2, U207.1 (A)
unnamed: R304.2, U303.A5 (CC1)
unnamed: R303.2, U303.B5 (CC2)
unnamed: C401.2, U401.9 (OSC1), X401.1 (OSC1)
unnamed: C403.2, U401.8 (OSC2), X401.2 (OSC2)
unnamed: C402.2, U402.9 (OSC1), X402.1 (OSC1)
unnamed: C404.2, U402.8 (OSC2), X402.2 (OSC2)
unnamed: R403.2, R404.2, U403.8 (STB)
unnamed: L401.1, U404.17 (CANH)
unnamed: L401.4, U404.15 (CANL)
unnamed: R407.1, U404.18 (RS)
unnamed: C420.2, C421.2, U404.12 (VISOOUT), U404.19 (VISOIN)
unnamed: C607.2, U601.4 (BST)
unnamed: C616.1, R604.1, R605.2, U601.1 (FB)
unnamed: C608.2, U602.4 (BST)
unnamed: C617.1, R606.1, R607.2, U602.1 (FB)
unnamed: R608.1, R609.2, U604.3 (EN/UVLO)
unnamed: R611.1, U604.6 (GATE)
unnamed: R610.1, U604.16 (RFB)
unnamed: R601.2, U604.14 (RREF)
unnamed: C625.2, R617.1, U604.7 (SENSE)
unnamed: C615.2, U604.10 (SS)
unnamed: R602.2, U604.12 (TC)
unnamed: C610.2, R603.2, U604.11 (VC)
unnamed: R619.2, U607.3 (EN)
unnamed: F601.2, R619.1, R620.1, U607.1 (VDD)
unnamed: R621.2, U608.3 (EN)
unnamed: F602.2, R621.1, R622.1, U608.1 (VDD)
unnamed: R624.2, U610.5 (DRAIN)
unnamed: C645.2, U610.3 (INTVCC)
unnamed: R626.2, U613.3 (EN)
unnamed: R627.2, U614.3 (EN)
OUTPUT: C201.1, R202.2, R203.2
PRECHARGE_ESP_SIGNAL: R211.1, U301.4 (IO4)
PRECHARGE_SENSE: C228.2, R244.2, R245.2, U301.39 (IO1)
RESET1: R402.1, U301.25 (IO48), U402.19 (RESET#)
RESET2: R401.1, U301.17 (IO9), U401.19 (RESET#)
SCHMITT_OUT: R206.2, U202.4 (Y), U301.5 (IO5)
SCK: U301.20 (IO12), U401.14 (SCK), U402.14 (SCK)
TEMP1_DQ: R501.1, U301.8 (IO15), U501.4 (DQ)
TEMP2_DQ: R502.1, U301.7 (IO7), U502.4 (DQ)
USBV: C307.2, D301.1 (A), D302.5, U302.8 (VBUS), U303.A4 (VBUS), U303.A9 (VBUS), U303.B4 (VBUS), U303.B9 (VBUS)

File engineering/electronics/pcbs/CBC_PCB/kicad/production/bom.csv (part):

"Designator","Footprint","Quantity","Value","LCSC Part #"
"C201","EasyEDA_Lib_2:CAP-SMD_BD6.3-L6.6-W6.6-LS7.4-FD","1","100uF","C1517616"
"C202,C632","EasyEDA_Lib:C0805","2","1uF","C5370002"
"C203,C204,C302,C305,C307,C407,C408,C414,C416,C420","EasyEDA_Lib:C0805","10","10uF","C440198"
"C205,C206,C207,C208,C601,C602,C603,C604,C644,C646","EasyEDA_Lib_2:C2220","10","2.2uF","C153032"
"C209,C210,C211,C212,C213,C214,C215,C216,C223,C224,C227,C605,C606,C607,C608,C616,C617,C626,C627,C634,C635,C639,C640","EasyEDA_Lib:C0603","23","100nF","C15725"
"C217,C218,C219,C220,C221,C222,C225,C226,C301,C405,C406,C412,C413,C618,C619,C620,C621,C622,C623","EasyEDA_Lib:C0805","19","4.7uF","C98192"
"C303","EasyEDA_Lib:C0402","1","1uF","C7472946"
"C304,C306,C409,C410,C421,C501,C502","EasyEDA_Lib:C0402","7","100nF","C60474"
"C401,C402,C403,C404","EasyEDA_Lib:C0402","4","22pF","C106203"
"C411,C415","Capacitor_SMD:C_0805_2012Metric_Pad1.18x1.45mm_HandSolder","2","100nF",""
"C417","EasyEDA_Lib_2:C0805","1","100pF","C599828"
"C418,C419,C422,C423","EasyEDA_Lib:C0402","4","220pF","C71693"
"C609","EasyEDA_Lib_2:CAP-SMD_BD10.0-L10.3-W10.3-FD-LS11.0","1","47uF","C49424130"
"C610","EasyEDA_Lib:C0805","1","470pF","C107138"
"C611,C612,C614,C624,C645","EasyEDA_Lib:C1206","5","4.7uF","C237304"
"C613","EasyEDA_Lib_2:C0805","1","33nF","C327114"
"C615","EasyEDA_Lib:C0603","1","220nF","C64705"
"C625","EasyEDA_Lib:C0603","1","47pF","C1671"
"C628","EasyEDA_Lib:C0603","1","4.7nF","C327158"
"C629,C630,C631,C633,C638,C641","EasyEDA_Lib:C1206","6","47uF","C403725"
"C636,C637,C642,C643","EasyEDA_Lib:CAP-SMD_L3.5-W2.8-R-RD","4","10uF","C7194"
"CN201","EasyEDA_Lib:CONN-SMD_A1257WV-S-2P","1","","C225118"
"D201,D202","EasyEDA_Lib_2:SOD-323_L1.8-W1.3-LS2.5-RD","2","","C2128"
"D203,D217","EasyEDA_Lib:SMB_L4.3-W3.6-LS5.4-BI","2","SMBJ78CA","C2903953"
"D204,D205,D208,D209,D210,D211,D214,D219","EasyEDA_Lib:SMB_L4.6-W3.6-LS5.4-BI","8","","C19077568"
"D206,D207","EasyEDA_Lib_2:SMA_L4.3-W2.6-LS5.2-RD","2","","C47779"
"D212,D213,D606,D607","EasyEDA_Lib:SMB_L4.6-W3.6-LS5.3-BI","4","","C83323"
"D215,D218","Diode_SMD:D_SMA","2","SS34",""
"D216","lcsc_footprints:C719814_TO-277A_L5_9-W4_4-LS6_5-TR","1","FSV10150V","C719814"
"D301","EasyEDA_Lib:SMA_L4.3-W2.6-LS5.0-FD","1","","C7420316"
"D302","EasyEDA_Lib:SOT-23-6_L2.9-W1.6-P0.95-LS2.8-BL","1","","C7519"
"D401,D403","Samacsys:DIONC1608X55N","2","PESD0603-240",""
"D402","EasyEDA_Lib_2:SOT-323-3_L2.0-W1.3-P1.30-LS2.1-BR","1","","C152727"
"D404","EasyEDA_Lib:SOT-23-3_L2.9-W1.3-P1.90-LS2.4-BL-2","1","","C14486"
"D601,D602","EasyEDA_Lib_2:SMB_L4.6-W3.6-LS5.3-RD","2","","C47124"
"D603","EasyEDA_Lib:SMB_L4.6-W3.6-LS5.3-RD","1","","C135108"
"D604","EasyEDA_Lib:SOD-123FL_L2.8-W1.8-LS3.8-RD","1","","C5354735"
"D605,D608","EasyEDA_Lib:SOD-123_L2.7-W1.6-LS3.7-RD-1","2","","C260853"
"D609","EasyEDA_Lib:SMB_L4.6-W3.6-LS5.3-RD","1","","C151789"
"D610","EasyEDA_Lib:SMB_L4.6-W3.6-LS5.3-RD","1","","C284082"
"F201,F603","EasyEDA_Lib:FUSE-SMD_L9.8-W5.1","2","0154005.DR","C206916"
"F202,F203,F601,F602","EasyEDA_Lib:FUSE-SMD_L9.8-W5.1","4","","C206908"
"H401,H402","EasyEDA_Lib:HDR-TH_2P-P2.54-V-M","2","","C492401"
"HC201,HC202","CBC_PCB:C90D_PAD","2","C90D_PAD",""
"J201,J202,J203,J204","CBC_PCB:AMT0650009DB0000G","4","AMT0650009DB0000G",""
"J501","CBC_PCB:B08B-JWPF-SK-R","1","B08B-JWPF-SK-R",""
"L201,L202","EasyEDA_Lib_2:IND-SMD_L5.0-W5.0-P3.60_SMNR5040","2","33uH","C9390"
"L401","EasyEDA_Lib:FILTER-SMD_4P-L4.5-W3.2_ACT45B-510-2P","1","","C48928226"
"L601","EasyEDA_Lib_2:IND-SMD_L6.6-W6.4","1","22uH","C5366013"
"L602,L603","EasyEDA_Lib_2:IND-SMD_L6.0-W6.0_SMNR6045","2","33uH","C135306"
"L604","EasyEDA_Lib:XFMR-SMD_12P-L22.1-W21.8-P3.00-LS29.2-BL","1","20.5uH","C5723154"
"LED201,LED202,LED203,LED301,LED601,LED602,LED603","EasyEDA_Lib:LED0603-RD","7","","C12624"
"Q201,Q205,Q206,Q207,Q208,Q209,Q210","EasyEDA_Lib:TOLL-8_L10.4-W9.9-P1.20-LS11.7-BL","7","","C22385354"
"Q202,Q203","lcsc_footprints:C2846922_SOT-323-3_L2_0-W1_3-P1_30-LS2_1-BR","2","LMUN5235T1G","C2846922"
"Q204","EasyEDA_Lib:TOLL-8_L10.4-W9.9-P1.20-LS11.7-BL","1","SP015N03BGHTO","C22385354"
"Q301","EasyEDA_Lib:SC-70-6_L2.2-W1.3-P0.65-LS2.1-BR","1","","C62892"
"Q601","CBC_PCB:DFN-8_L5.9-W5.2-P1.27-LS6.2-BL","1","","C501501"
"Q602","CBC_PCB:DFN-8_L5.9-W5.2-P1.27-LS6.2-BL","1","","C501500"
"R201,R207,R212,R217,R223,R226,R227,R235,R237,R242,R301,R401,R402","EasyEDA_Lib:R0402","13","10kΩ","C190095"
"R202","EasyEDA_Lib_2:R0805","1","15kΩ","C114559"
"R203","EasyEDA_Lib_2:R0805","1","120kΩ","C114524"
"R204","EasyEDA_Lib_2:R0805","1","36kΩ","C114527"
"R205","EasyEDA_Lib_2:R0805","1","10kΩ","C84376"
"R206","EasyEDA_Lib:R0402","1","330Ω","C105875"
"R208,R209","EasyEDA_Lib:R2512","2","10Ω","C47019"
"R210,R214,R218,R225,R228,R236,R240","lcsc_footprints:C25076_R0402","7","100Ω","C25076"
"R211,R213","lcsc_footprints:C106231_R0402","2","0","C106231"
"R215,R216","lcsc_footprints:C114617_R0603","2","300","C114617"
"R219,R221","EasyEDA_Lib:R0603","2","590K, 0603",""
"R220,R222,R232,R234,R605,R607,R614,R616","EasyEDA_Lib:R0603","8","10kΩ","C95204"
"R224","lcsc_footprints:C125758_R0603","1","20","C125758"
"R229,R230","EasyEDA_Lib:RES-TH_BD7.5-L20.0-P24.00-D1.0","2","33Ω","C511506"
"R231,R233,R613,R615","EasyEDA_Lib:R0603","4","140kΩ","C47115952"
"R238,R239,R241,R625","EasyEDA_Lib:R0603","4","1.8kΩ","C4177"
"R302","EasyEDA_Lib:R0603","1","39Ω","C23154"
"R303,R304","EasyEDA_Lib:R0402","2","5.1kΩ","C25905"
"R403","Resistor_SMD:R_0805_2012Metric_Pad1.20x1.40mm_HandSolder","1","0R",""
"R404","Resistor_SMD:R_0805_2012Metric_Pad1.20x1.40mm_HandSolder","1","10K",""
"R405,R408","EasyEDA_Lib:R0603","2","120Ω","C22787"
"R406","EasyEDA_Lib_2:R0805","1","1MΩ","C107700"
"R407,R611","EasyEDA_Lib:R0402","2","0Ω","C106231"
"R501,R502","EasyEDA_Lib:R0402","2","4.7kΩ","C105871"
"R601","EasyEDA_Lib:R0603","1","6.04kΩ","C25977"
"R602","EasyEDA_Lib:R0603","1","60.4kΩ","C23089"
"R603","EasyEDA_Lib:R0603","1","7.5kΩ","C2930127"
"R604,R606","EasyEDA_Lib:R0603","2","240kΩ","C705831"
"R608","EasyEDA_Lib:R0805","1","1.2MΩ","C2933294"
"R609","EasyEDA_Lib:R0603","1","51kΩ","C351642"
"R610","EasyEDA_Lib:R0805","1","160kΩ","C17485"
"R612","EasyEDA_Lib:R0805","1","68Ω","C445645"
"R617,R623","EasyEDA_Lib:R0805","2","3Ω","C17660"
"R618,R619,R621,R626,R627","EasyEDA_Lib:R0603","5","100Ω","C394538"
"R620,R622","EasyEDA_Lib:R0603","2","390Ω","C23151"
"R624","EasyEDA_Lib:R0603","1","2.37kΩ","C2933174"
"SW301","EasyEDA_Lib:SW-SMD_L3.9-W3.0-P4.45","1","","C720477"
"U201","EasyEDA_Lib:UDFN-8_L1.5-W1.0-P0.35-BL","1","74LVC2G02HK3-7","C842632"
"U202","EasyEDA_Lib:SOT-25-5_L3.0-W1.8-P0.95-LS3.0-BL","1","74LVC1G17W5-7","C151394"
"U203","EasyEDA_Lib:SOP-4_L4.1-W3.8-P2.54-LS6.1-BL","1","CPC1106NTR","C5341660"
"U204,U205,U601,U602","CBC_PCB:SOIC-8EP_MP9486_MNP","4","MP9486GN-Z",""
"U206,U207","lcsc_footprints:C42432174_SOP-6_L6_8-W4_6-P1_27-LS11_7-BL","2","ICPL-314P-500EAXW","C42432174"
"U208,U209","CBC_PCB:SMD_BD6.0-D4.2","2","BSMTSOM330BTR","C20617225"
"U301","EasyEDA_Lib:WIRELM-SMD_ESP32-S3-WROOM-1","1","2.4GHz","C2913202"
"U302","EasyEDA_Lib:QFN-24_L4.0-W4.0-P0.50-BL-EP2.7","1","","C47742"
"U401,U402","EasyEDA_Lib:TSSOP-20_L6.5-W4.4-P0.65-LS6.4-BL","2","","C185941"
"U403","Samacsys:SOIC127P600X175-8N","1","TJA1049T/3J",""
"U404","EasyEDA_Lib:SOIC-20_L13.0-W7.6-P1.27-LS10.3-BL","1","ADM3053BRWZ-REEL7","C117821"
"U501,U502","EasyEDA_Lib:SOIC-8_L4.9-W3.9-P1.27-LS6.0-BL","2","","C97190"
"U603","EasyEDA_Lib_2:C0805","1","1uF","C5370002"
"U604","EasyEDA_Lib:MSOP-16_12P-L4.0-W3.0-P0.50-LS4.9-BL","1","","C117158"
"U605","EasyEDA_Lib:C0603","1","120pF","C1864338"
"U606","EasyEDA_Lib:R1206","1","10mΩ","C20608707"
"U607,U608,U613,U614","EasyEDA_Lib:MAX40203AUK_T_SOT-23-5","4","MAX40203AUK+T","C2653639"
"U609","EasyEDA_Lib:IND-SMD_L6.6-W6.4_XAL6060-103ME","1","1uH","C2938919"
"U610","EasyEDA_Lib:TSOT-23-5_L2.9-W1.6-P0.95-LS2.8-BR","1","","C580284"
"U611,U612","EasyEDA_Lib:SOT-223-3_L6.5-W3.4-P2.30-LS7.0-BR","2","","C6186"
"USB301","EasyEDA_Lib_2:USB-C-SMD_TYPEC-303-ACP16","1","","C720628"
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
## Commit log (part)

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2026-03-30 ci: terraform provisioned file changes
    [skip ci]
2026-03-30 fixup! ci: terraform provisioned file changes
    [skip ci]
2026-03-30 docs: add project README
    Covers project overview, mission profile, design philosophy,
    phase breakdown, governance, deliverables, and regulatory strategy.
    Based on the AIP-006 proposal and Project Caribou forum discussion:
    https://dao.arrowair.com/t/project-caribou-discussion-heavy-lift-hexacopter/150
2026-03-30 docs: simplify README to key specs and features
2026-03-30 docs: simplify README — key aspects only, no phases or cost
2026-03-30 docs: add concept render to README
2026-03-30 docs: fix spelling check and broken LICENSE link
    - Add 'hexacopter' to project words list
    - Replace local LICENSE link with CERN URL (file not yet in repo)
2026-03-30 fix: add remaining project words to cspell list
2026-03-30 docs: add remaining flagged words to cspell project words
2026-04-01 docs: add PT1 documentation structure
    - docs/pt1/001-engineering-report/engineering-report.md
    - docs/pt1/002-manufacturing-guides/frame-assembly.md
    - docs/pt1/003-user-guides/maintenance-guide.md
    All placeholder content, ready to fill in.
2026-04-01 docs: rename frame-assembly to structural-assembly
2026-04-10 docs: add battery position reference image for issue #9
2026-04-13 docs: add Fusion 360 workspace readme
    Folder structure, naming convention, workflow rules, and access
    guidelines from issue #4.
2026-04-28 chore: add engineering project structure
2026-04-28 chore: update pcb project layout
2026-04-28 docs: add CBC PCB design notes
2026-04-28 chore: add CBC spelling terms
2026-04-28 docs: add CBC PCB renderings
2026-05-05 docs: update C90D PCB readme from issue
2026-05-05 chore: fix CMAIN docs spelling
2026-05-05 docs: add ESC cable drawing reference
2026-05-05 CMAIN initial fork from Quiver Main PCB
2026-05-05 docs: add clean CMAIN KiCad fork
2026-05-05 chore: exclude KiCad generated files from text checks
2026-05-07 Import linked CMAIN PCB layout
2026-05-18 Add CBC PCB issue reference images
2026-05-19 Add initial CBC PCB KiCad layout
2026-05-19 chore: exclude STEP exports from text checks
2026-05-19 fix: restore CBC schematic library nicknames
2026-05-19 fix: add C90D pad library aliases
2026-05-19 fix: qualify CBC connector footprint refs
2026-05-23 fix: align CBC schematic connections to grid
2026-05-23 fix: assign CBC imported symbol pin types
2026-05-23 fix: clean CBC KiCad library references
2026-05-23 fix: make CBC EasyEDA footprint library loadable
2026-05-23 fix: add CBC peripheral sensor power flag
2026-05-23 fix: include updated CBC power section
2026-05-23 feat: add MAX40203 ORing controller library part
2026-05-23 docs: capture CBC schematic review follow-ups
2026-05-23 electronics: update CBC redundant power regulators
2026-05-24 fix: align CBC schematics to KiCad grid
2026-05-25 electronics: integrate CBC PCB updates
2026-05-25 electronics: update CBC PCB and crystal parts
2026-05-25 electronics: add missing C1206 3D model
2026-05-26 electronics: integrate CBC PCB footprint updates
2026-05-26 electronics: fix CBC footprint component types
2026-05-26 electronics: fix CBC 3D model references
2026-05-26 electronics: clear CBC silkscreen copper warnings
2026-05-26 electronics: integrate final CBC PCB routing update
2026-05-26 ci: fix sanity check configuration for CBC PR
2026-06-01 electronics: update CMAIN and CBC PCB files
2026-06-02 electronics: integrate C90D PCB v1.1 files
2026-06-02 electronics: add C20617225 3D model
2026-06-02 electronics: integrate June PCB updates
2026-06-02 electronics: clean up CMAIN local libraries
2026-06-02 electronics: snap CMAIN schematic endpoints to grid
2026-06-04 feat: integrate June PCB updates
2026-06-10 pcb: update CBC import and routing rules
2026-06-10 pcb: normalize CBC routed trace widths
2026-06-10 sch: fix simple CBC ERC issues
2026-06-10 pcb: enable netclass-based routing width
2026-06-10 ci: ignore generated KiCad artifacts in cspell
2026-06-10 ci: ignore CBC generated KiCad files in cspell
2026-06-10 ci: add KiCad table tokens to cspell words
2026-06-12 electronics: update CMAIN PCB from June layout
2026-06-12 electronics: resolve available CMAIN 3D models
2026-06-12 electronics: add available CMAIN JLC 3D models
2026-06-12 electronics: map CMAIN standard 3D model refs
2026-06-15 electronics: vendor CMAIN EasyEDA footprints
2026-06-15 Revert "electronics: vendor CMAIN EasyEDA footprints"
    This reverts commit 9d702adc658192e84b57025cf413e62d678808d8.
2026-06-15 electronics: shorten CMAIN footprint filenames for Windows
2026-06-15 electronics: integrate CMAIN STEP updates and consolidate footprints
2026-06-15 docs: add CMAIN 3D viewer link
2026-06-15 docs: clean up CMAIN wording
2026-06-15 Fix CMAIN schematic embedded symbol name
2026-06-15 Resolve CMAIN ERC warnings
2026-06-15 Apply CMAIN PCB routing rule classes
2026-06-15 Exclude generated PCB artifacts from cspell
2026-06-16 Update CMAIN PCB routing from latest archive
    Import Julius's latest CMAIN KiCad update, excluding local .history and backup archives. Remap undefined Rescue footprint graphics to F.Fab so KiCad CLI can load the board, and add KiCad ERC/DRC repo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
2026-06-16 Add CMAIN report terms to spelling dictionary
2026-06-18 Clean up CMAIN part value fields
2026-06-23 fix(cmain): import KiCad updates with native libs
2026-06-29 fix(cmain): integrate prototype ordering update
2026-06-29 ci: ignore generated CMAIN production outputs
2026-06-29 fix(cmain): mark GH connector pins passive
2026-06-30 fix(cbc): integrate ordered PCB update
